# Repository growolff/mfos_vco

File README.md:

# mfos_vco

* Based in [Ray Wilson's VCO published in Music From Outter space VCO](https://musicfromouterspace.com/analogsynth_new/VCO20090724REV0/VCO20090724REV0.html)
* Created in Kicad

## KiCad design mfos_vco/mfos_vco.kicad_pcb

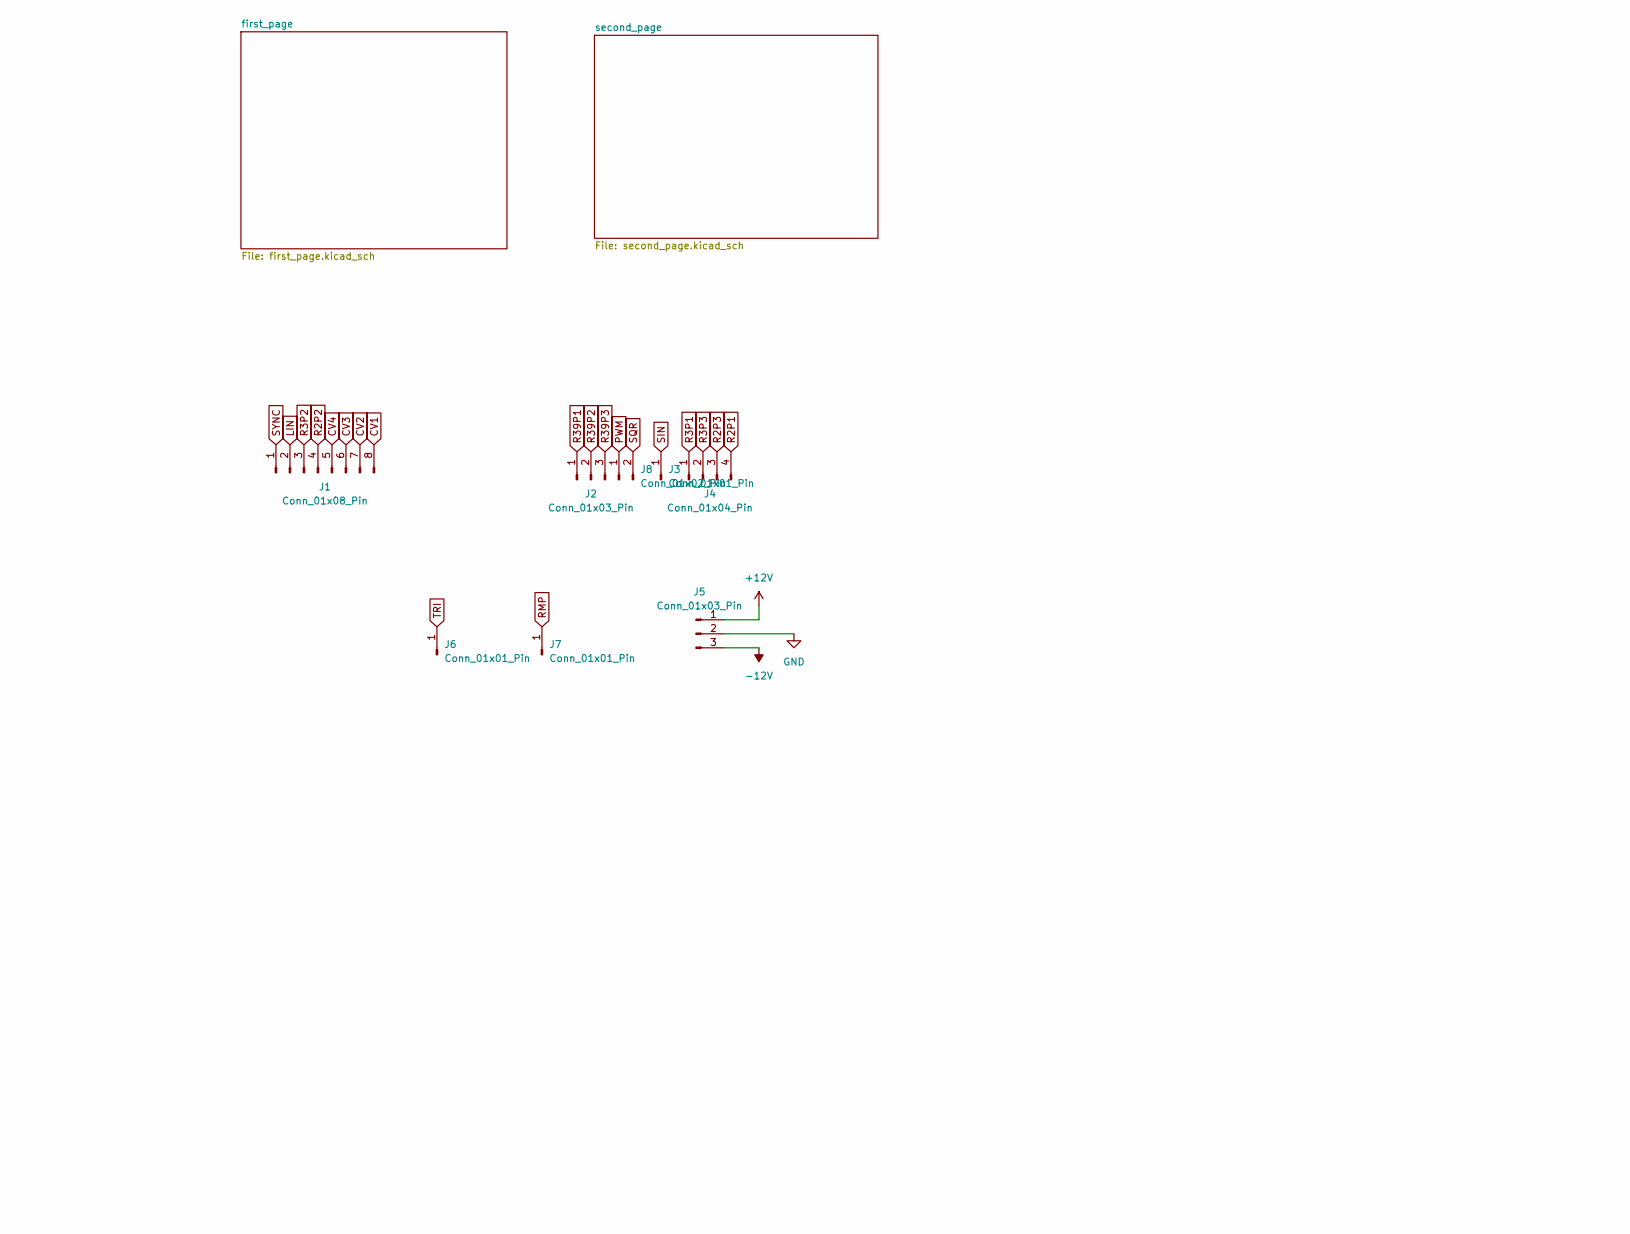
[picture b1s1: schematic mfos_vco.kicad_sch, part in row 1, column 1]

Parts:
J1: Conn_01x08_Pin; PinSocket_1x08_P2.54mm_Vertical
J2, J5: Conn_01x03_Pin; PinSocket_1x03_P2.54mm_Vertical
J3, J6, J7: Conn_01x01_Pin; PinSocket_1x01_P2.54mm_Vertical
J4: Conn_01x04_Pin; PinSocket_1x04_P2.54mm_Vertical
J8: Conn_01x02_Pin; PinSocket_1x02_P2.54mm_Vertical

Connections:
+12V: J5.1; also elsewhere on the board
-12V: J5.3; also elsewhere on the board
CV1: J1.8; also elsewhere on the board
CV2: J1.7; also elsewhere on the board
CV3: J1.6; also elsewhere on the board
CV4: J1.5; also elsewhere on the board
GND: J5.2; also elsewhere on the board
LIN: J1.2; also elsewhere on the board
PWM: J8.1; also elsewhere on the board
R2P1: J4.4; also elsewhere on the board
R2P2: J1.4; also elsewhere on the board
R2P3: J4.3; also elsewhere on the board
R3P1: J4.1; also elsewhere on the board
R3P2: J1.3; also elsewhere on the board
R3P3: J4.2; also elsewhere on the board
R39P1: J2.1; also elsewhere on the board
R39P2: J2.2; also elsewhere on the board
R39P3: J2.3; also elsewhere on the board
RMP: J7.1; also elsewhere on the board
SIN: J3.1; also elsewhere on the board
SQR: J8.2; also elsewhere on the board
SYNC: J1.1; also elsewhere on the board
TRI: J6.1; also elsewhere on the board

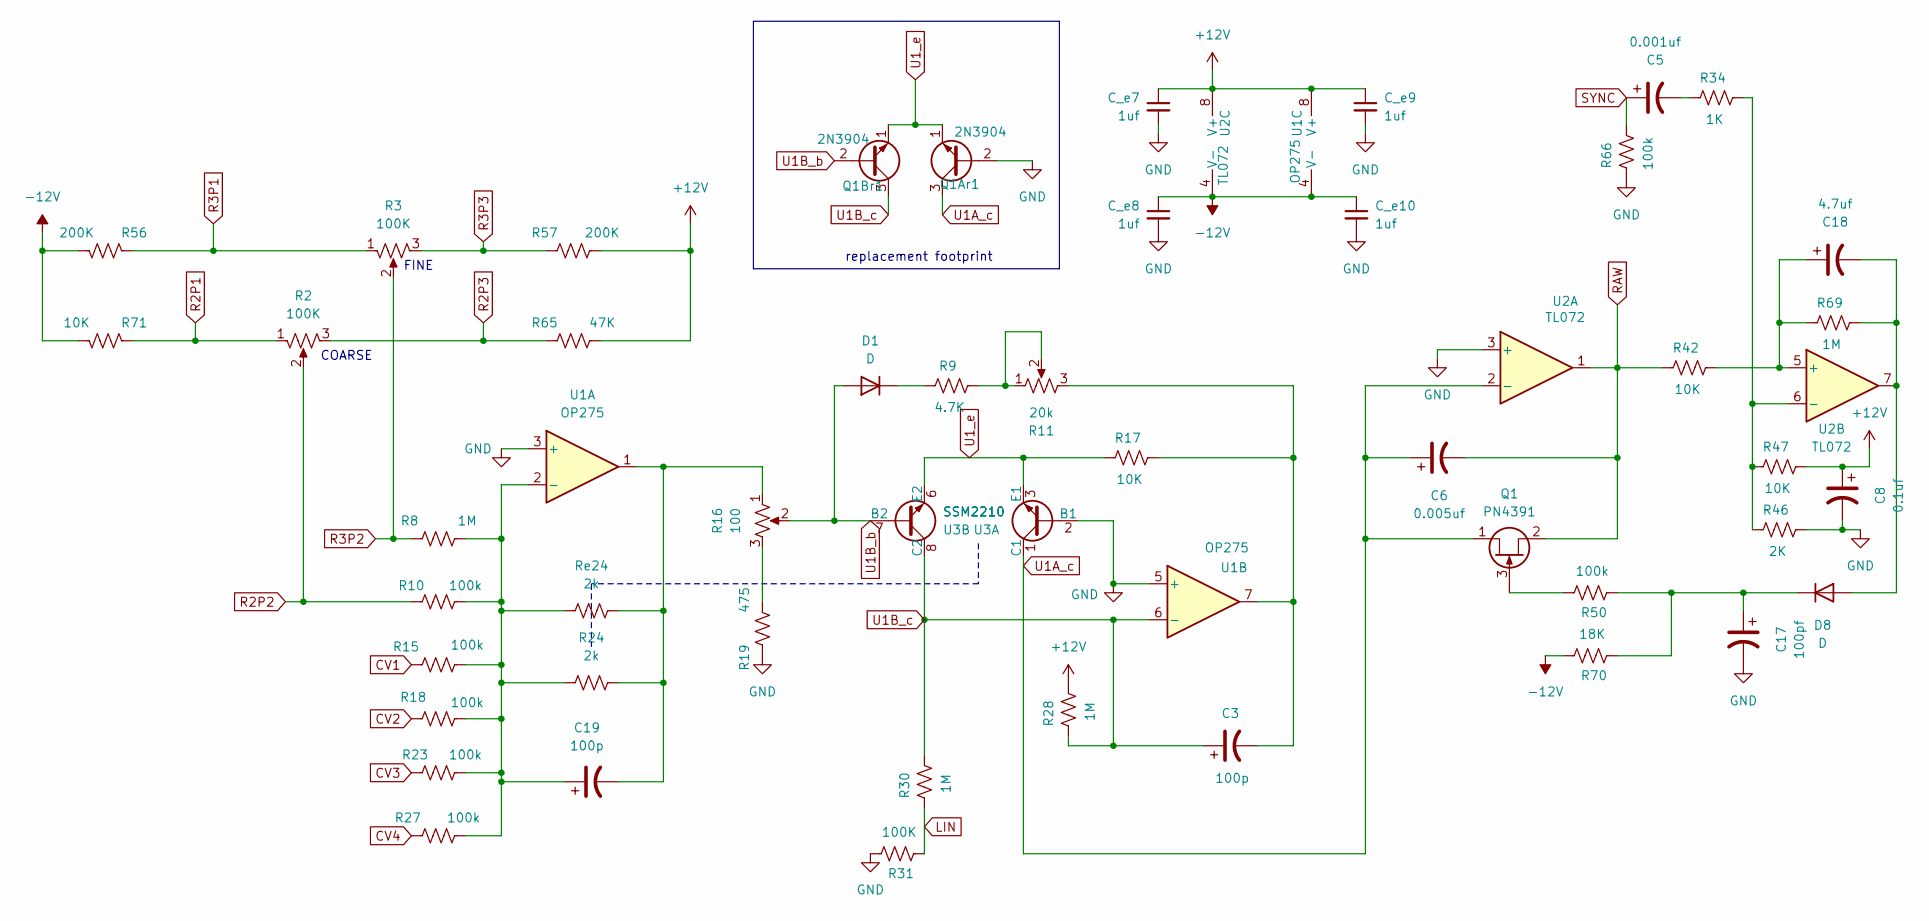
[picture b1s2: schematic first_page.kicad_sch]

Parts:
C3, C19: 100p; cp_p5.0
C5: 0.001uf; cp_p5.0
C6: 0.005uf; cp_p5.0
C8: 0.1uf; cp_p5.0
C17: 100pf; cp_p5.0
C18: 4.7uf; cp_p5.0
C_e7, C_e8, C_e9, C_e10: 1uf; C_0805_2012Metric_Pad1.18x1.45mm_HandSolder
D1, D8: D; D_T-1_P5.08mm_Horizontal
Q1: PN4391; TO-92L_Inline_Wide
Q1Ar1, Q1Br1: 2N3904; TO-92L_Inline_Wide
R2, R3: 100K
R8, R28, R30, R69: 1M; R_SMD_AND_THT
R9: 4.7K; R_SMD_AND_THT
R10, R15, R18, R23, R27, R50, R66: 100k; R_SMD_AND_THT
R11: 20k; Potentiometer_Bourns_3296W_Vertical
R16: 100; Potentiometer_Bourns_3296W_Vertical
R17, R42, R47, R71: 10K; R_SMD_AND_THT
R19: 475; R_SMD_AND_THT
R24: 2k; R_SMD_AND_THT
R31: 100K; R_SMD_AND_THT
R34: 1K; R_SMD_AND_THT
R46: 2K; R_SMD_AND_THT
R56, R57: 200K; R_SMD_AND_THT
R65: 47K; R_SMD_AND_THT
R70: 18K; R_SMD_AND_THT
Re24: 2k; R_Axial_DIN0516_L15.5mm_D5.0mm_P20.32mm_Horizontal
U1: OP275; DIP-8_W7.62mm
U2: TL072; DIP-8_W7.62mm
U3: SSM2210; DIP-8_W7.62mm

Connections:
+12V: C8.1, C_e7.1, C_e9.1, R28.1, R47.1, R57.2, R65.2, U1.8 (V+), U2.8 (V+); also elsewhere on the board
-12V: C_e8.1, C_e10.1, R56.2, R70.1, R71.2, U1.4 (V-), U2.4 (V-); also elsewhere on the board
CV1: R15.1; also elsewhere on the board
CV2: R18.1; also elsewhere on the board
CV3: R23.1; also elsewhere on the board
CV4: R27.1; also elsewhere on the board
GND: C8.2, C17.2, C_e7.2, C_e8.2, C_e9.2, C_e10.2, Q1Ar1.2 (B), R19.1, R31.1, R46.1, R66.2, U1.3 (+), U1.5 (+), U2.3 (+), U3.2 (B1); also elsewhere on the board
LIN: R30.2, R31.2; also elsewhere on the board
unnamed: C3.2, R11.3, R17.1, U1.7
unnamed: C5.2, R34.2
unnamed: C19.2, R16.1, R24.2, Re24.2, U1.1
unnamed: D1.1 (K), R9.2
unnamed: C18.2, D8.2 (A), R69.1, U2.7
unnamed: C17.1, D8.1 (K), R50.2, R70.2
unnamed: Q1.3 (G), R50.1
unnamed: R9.1, R11.1, R11.2
unnamed: R16.3, R19.2
unnamed: C19.1, R8.2, R10.2, R15.2, R18.2, R23.2, R24.1, R27.2, Re24.1, U1.2 (-)
unnamed: C18.1, R42.1, R69.2, U2.5 (+)
unnamed: R34.1, R46.2, R47.2, U2.6 (-)
R2P1: R2.1, R71.1; also elsewhere on the board
R2P2: R2.2, R10.1; also elsewhere on the board
R2P3: R2.3, R65.1; also elsewhere on the board
R3P1: R3.1, R56.1; also elsewhere on the board
R3P2: R3.2, R8.1; also elsewhere on the board
R3P3: R3.3, R57.1; also elsewhere on the board
RAW: C6.2, Q1.2 (S), R42.2, U2.1; also elsewhere on the board
SYNC: C5.1, R66.1; also elsewhere on the board
U1A_c: C6.1, Q1.1 (D), Q1Ar1.3 (C), U2.2 (-), U3.1 (C1)
U1B_b: D1.2 (A), Q1Br1.2 (B), R16.2, U3.7 (B2)
U1B_c: C3.1, Q1Br1.3 (C), R28.2, R30.1, U1.6 (-), U3.8 (C2)
U1_e: Q1Ar1.1 (E), Q1Br1.1 (E), R17.2, U3.3 (E1), U3.6 (E2)

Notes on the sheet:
FINE
COARSE
replacement footprint

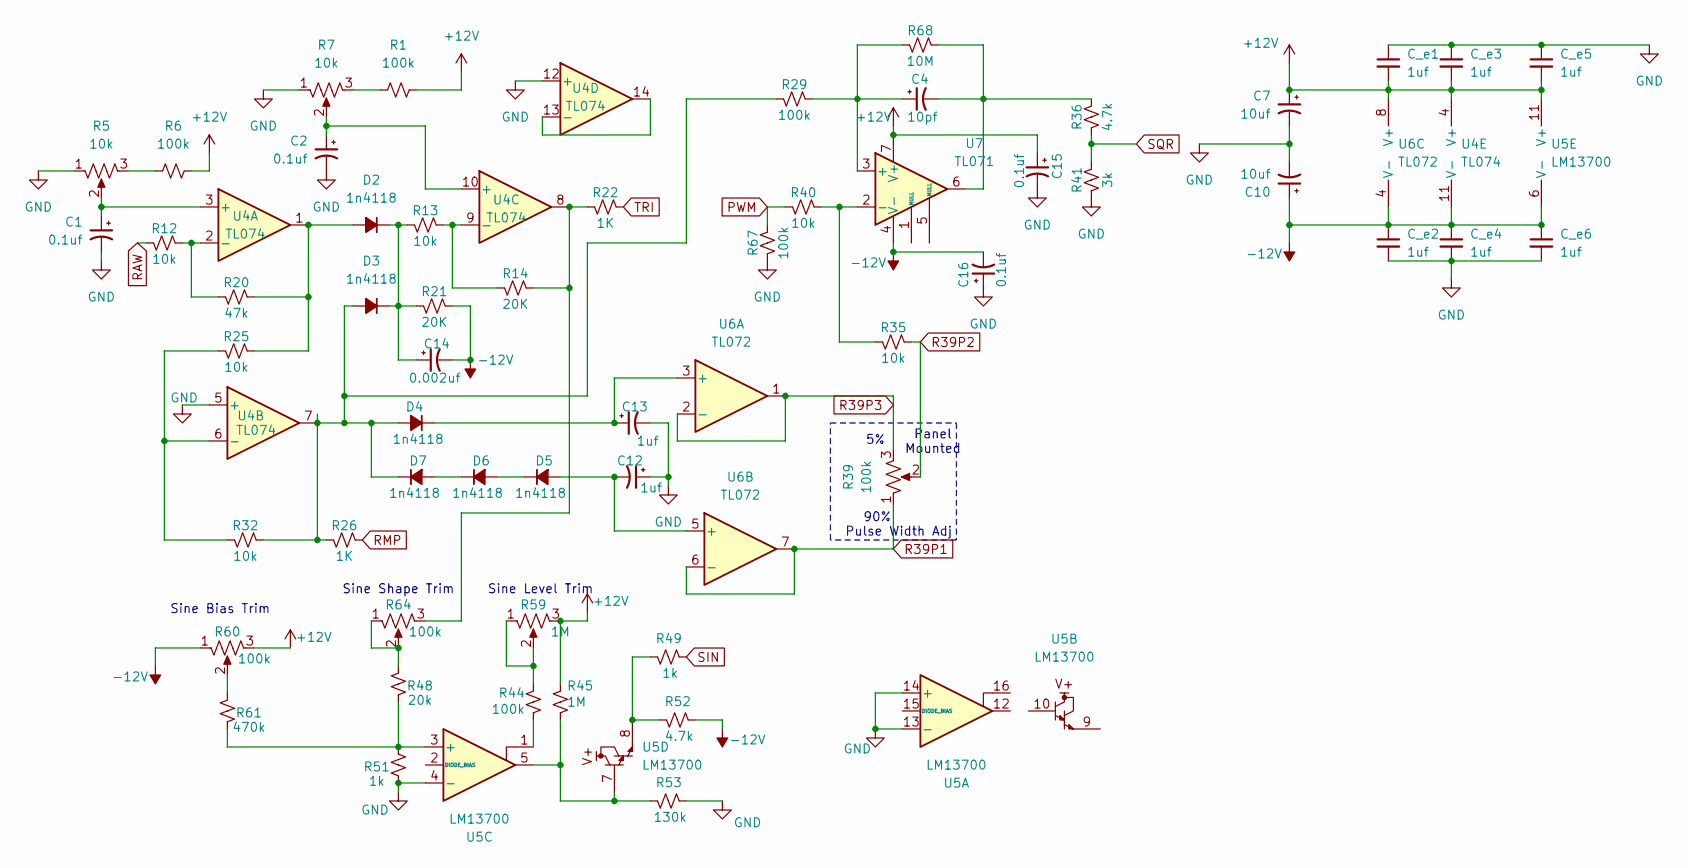
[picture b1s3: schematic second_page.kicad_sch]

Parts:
C1, C2, C15, C16: 0.1uf; cp_p5.0
C4: 10pf; cp_p5.0
C7, C10: 10uf; CP_Radial_Tantal_D4.5mm_P5.00mm
C12, C13: 1uf; CP_Radial_Tantal_D4.5mm_P5.00mm
C14: 0.002uf; cp_p5.0
C_e1, C_e2, C_e3, C_e4, C_e5, C_e6: 1uf; C_0805_2012Metric_Pad1.18x1.45mm_HandSolder
D2, D3, D4, D5, D6, D7: 1n4118; D_T-1_P5.08mm_Horizontal
R1, R6, R29, R44, R67: 100k; R_SMD_AND_THT
R5, R7: 10k; Potentiometer_Bourns_3296W_Vertical
R12, R13, R25, R32, R35, R40: 10k; R_SMD_AND_THT
R14, R21: 20K; R_SMD_AND_THT
R20: 47k; R_SMD_AND_THT
R22, R26: 1K; R_SMD_AND_THT
R36, R52: 4.7k; R_SMD_AND_THT
R39: 100k
R41: 3k; R_SMD_AND_THT
R45: 1M; R_SMD_AND_THT
R48: 20k; R_SMD_AND_THT
R49, R51: 1k; R_SMD_AND_THT
R53: 130k; R_SMD_AND_THT
R59: 1M; Potentiometer_Bourns_3296W_Vertical
R60, R64: 100k; Potentiometer_Bourns_3296W_Vertical
R61: 470k; R_SMD_AND_THT
R68: 10M; R_SMD_AND_THT
U4: TL074; DIP-14_W7.62mm
U5: LM13700; DIP-16_W7.62mm
U6: TL072; DIP-8_W7.62mm
U7: TL071; DIP-8_W7.62mm

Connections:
+12V: C7.1, C15.1, C_e1.2, C_e3.2, C_e5.2, R1.2, R6.2, R45.2, R59.3, R60.3, U4.4 (V+), U5.11 (V+), U6.8 (V+), U7.7 (V+); also elsewhere on the board
-12V: C10.1, C14.2, C16.2, C_e2.1, C_e4.1, C_e6.1, R21.2, R52.1, R60.1, U4.11 (V-), U5.6 (V-), U6.4 (V-), U7.4 (V-); also elsewhere on the board
GND: C1.2, C2.2, C7.2, C10.2, C12.1, C13.2, C15.2, C16.1, C_e1.1, C_e2.2, C_e3.1, C_e4.2, C_e5.1, C_e6.2, R5.1, R7.1, R41.1, R51.1, R53.1, R67.1, U4.5 (+), U4.12 (+), U5.4 (-), U5.13 (-), U5.14 (+); also elsewhere on the board
unnamed: C4.2, R36.2, R68.2, U7.6
unnamed: D2.2 (A), R20.2, R25.2, U4.1
unnamed: C14.1, D2.1 (K), D3.1 (K), R13.1, R21.1
unnamed: D3.2 (A), D4.2 (A), D7.1 (K), R26.1, R29.1, R32.2, U4.7
unnamed: C13.1, D4.1 (K), U6.3 (+)
unnamed: C12.2, D5.2 (A), U6.5 (+)
unnamed: D5.1 (K), D6.2 (A)
unnamed: D6.1 (K), D7.2 (A)
unnamed: R1.1, R7.3
unnamed: R5.3, R6.1
unnamed: R14.2, R22.1, R64.3, U4.8
unnamed: R44.1, U5.1
unnamed: R44.2, R59.1, R59.2
unnamed: R45.1, R53.2, U5.5, U5.7
unnamed: R48.2, R64.1, R64.2
unnamed: R49.2, R52.2, U5.8
unnamed: R60.2, R61.2
unnamed: C1.1, R5.2, U4.3 (+)
unnamed: R12.2, R20.1, U4.2 (-)
unnamed: R25.1, R32.1, U4.6 (-)
unnamed: C2.1, R7.2, U4.10 (+)
unnamed: R13.2, R14.1, U4.9 (-)
unnamed: U4.13 (-), U4.14
unnamed: R48.1, R51.2, R61.1, U5.3 (+)
unnamed: C4.1, R29.2, R68.1, U7.3 (+)
unnamed: R35.1, R40.2, U7.2 (-)
PWM: R40.1, R67.2; also elsewhere on the board
R39P1: R39.1, U6.6 (-), U6.7; also elsewhere on the board
R39P2: R35.2, R39.2; also elsewhere on the board
R39P3: R39.3, U6.1, U6.2 (-); also elsewhere on the board
RAW: R12.1; also elsewhere on the board
RMP: R26.2; also elsewhere on the board
SIN: R49.1; also elsewhere on the board
SQR: R36.1, R41.2; also elsewhere on the board
TRI: R22.2; also elsewhere on the board

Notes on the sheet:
Sine Bias Trim
Panel Mounted
Sine Shape Trim
Pulse Width Adj
Sine Level Trim
90%

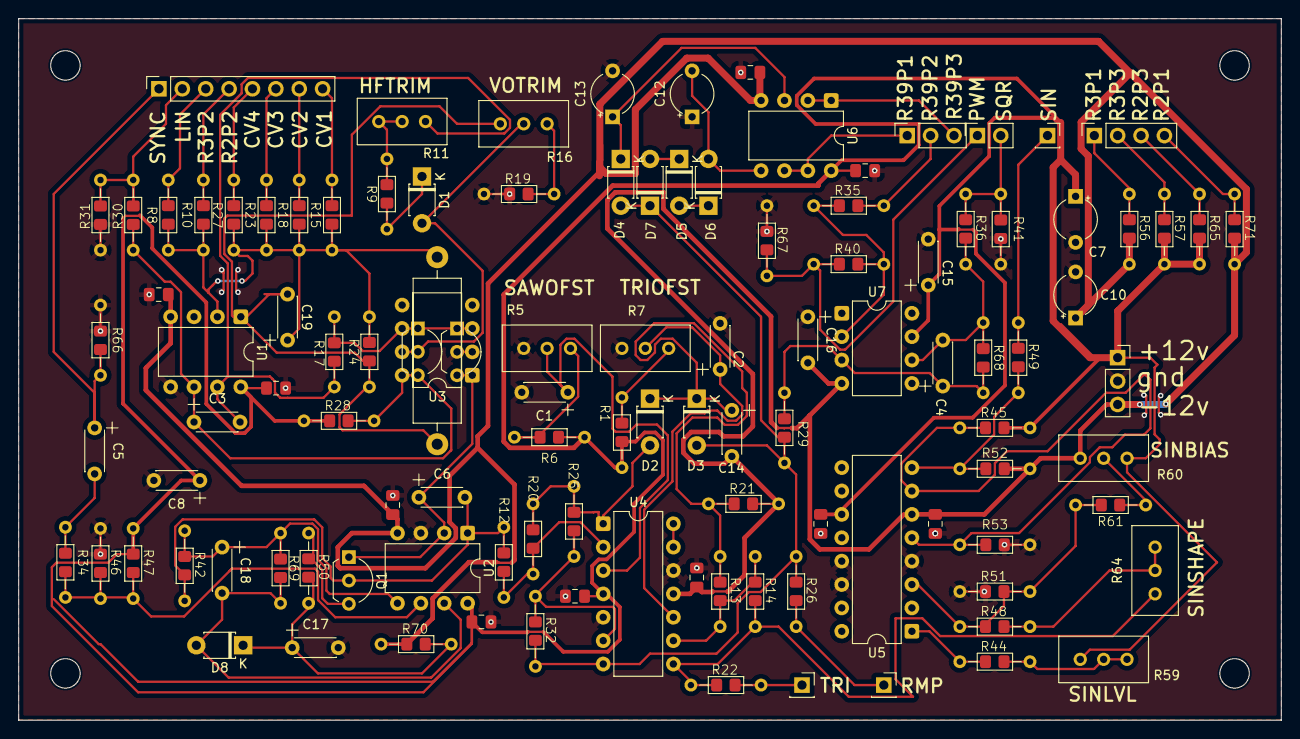
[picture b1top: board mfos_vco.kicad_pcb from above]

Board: 2 copper layers, 137.2 x 76.2 mm, 112 parts (0 on the bottom side), 66 nets.

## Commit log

2024-11-21 first schematic update
2024-11-21 Second Commit
    nueva hoja
2025-05-12 added gitignore and updated to kicad 9
2025-05-12 finished first page. Added hierarchical sheets for first and second page
2025-05-13 Firs stages of second page
2025-05-13 finished second page of schematic
2025-05-13 Added output jumpers and custom foorprint
2025-05-13 added footprints
2025-05-14 Finished placing components. Added a reference pic and footprint for the original design
2025-05-14 first partial routing
2025-05-14 routing again
2025-05-15 FINISHED ROUTING
